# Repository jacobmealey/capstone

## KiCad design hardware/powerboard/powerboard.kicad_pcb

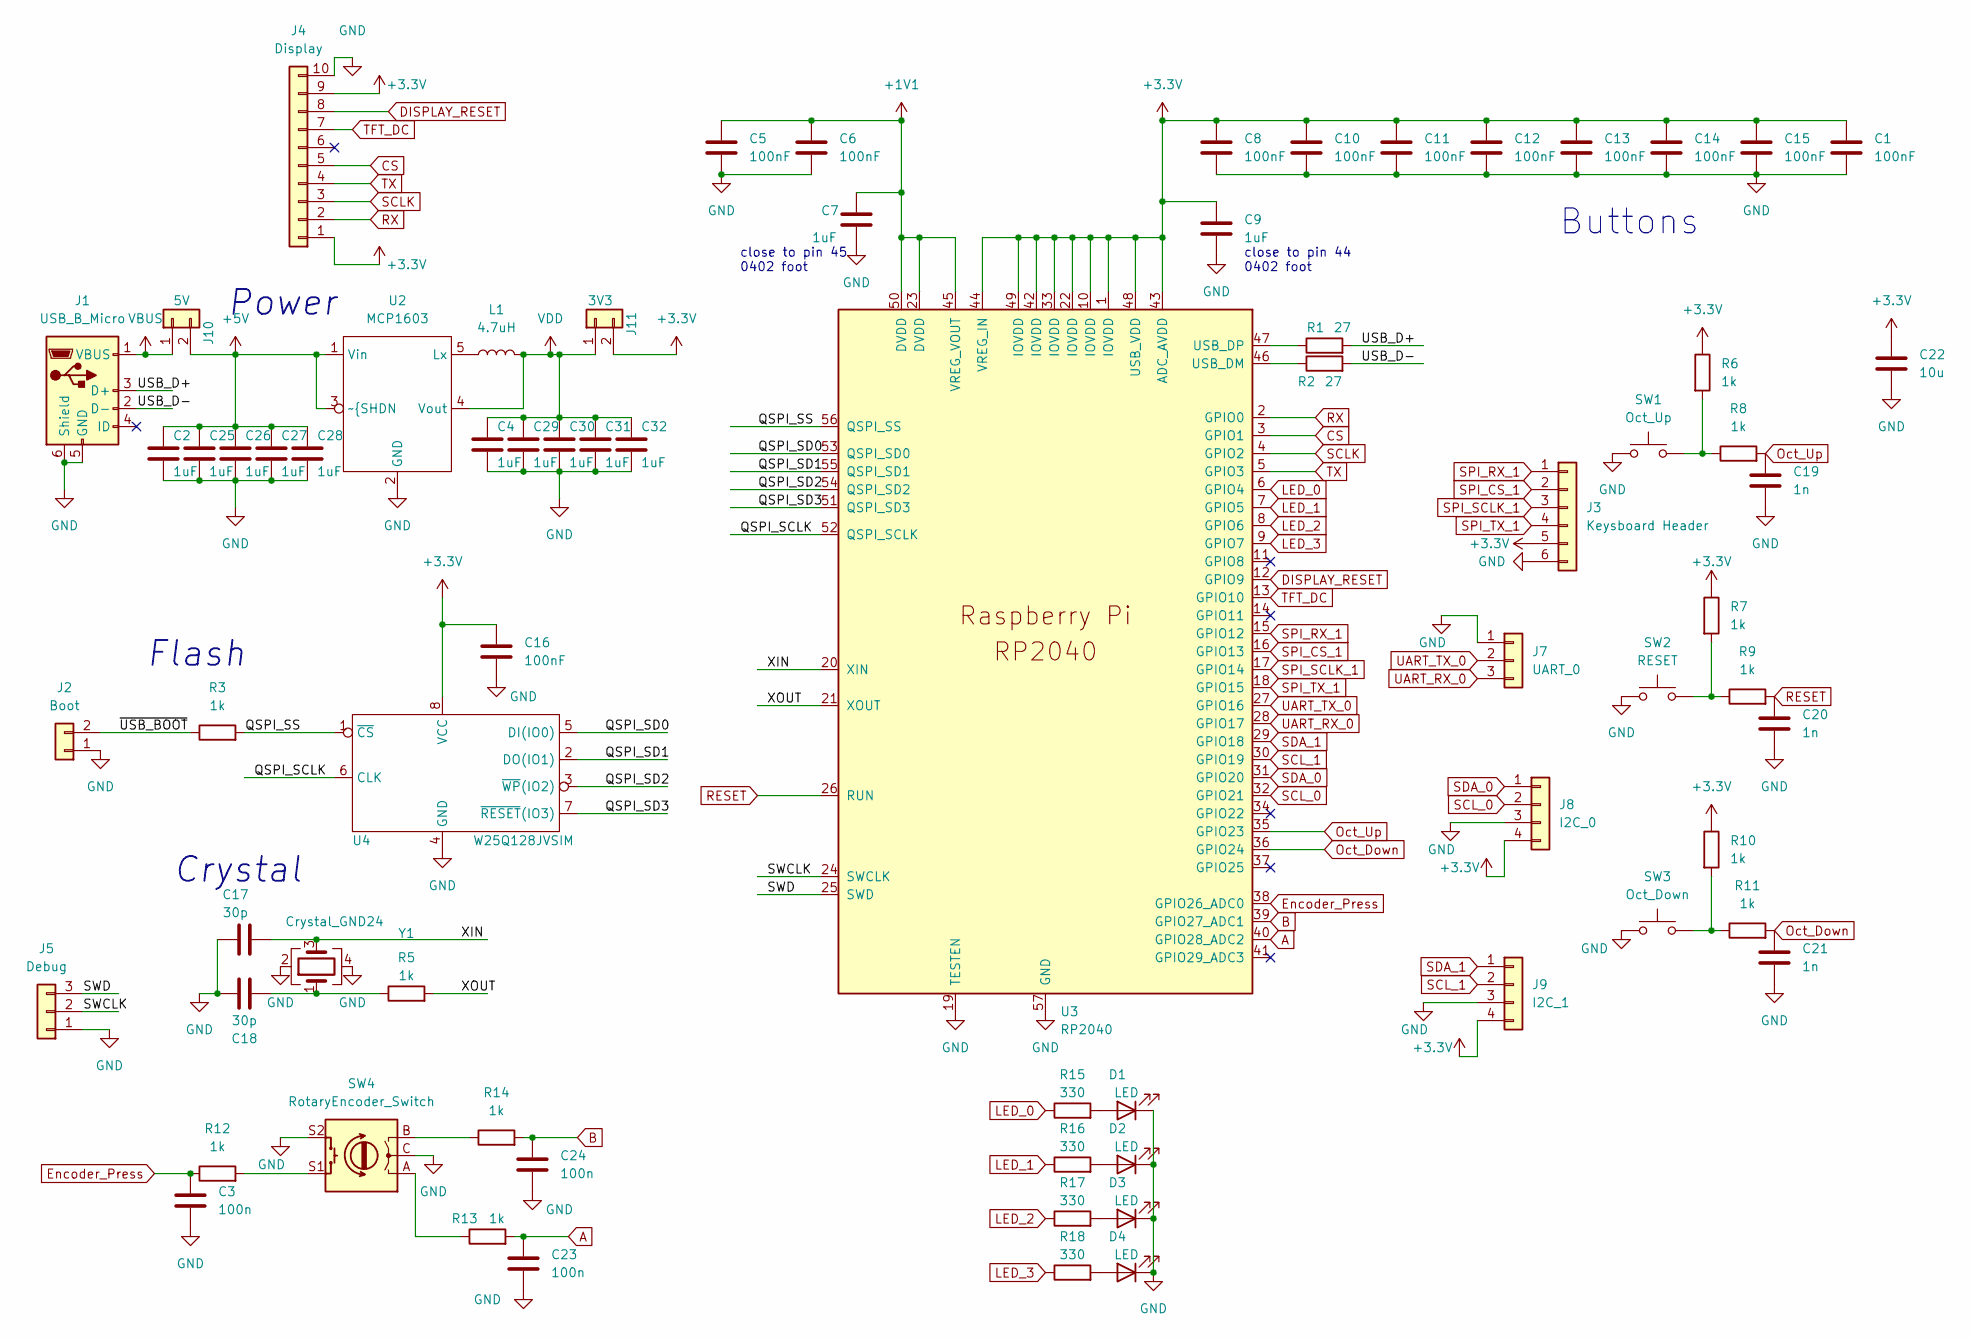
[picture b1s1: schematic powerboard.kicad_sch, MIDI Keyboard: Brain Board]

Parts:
C1, C5, C6, C8, C10, C11, C12, C13, C14, C15: 100nF; C_0402_1005Metric; LCSC C307331
C2, C4, C25, C26, C27, C28, C29, C30, C31, C32: 1uF; C_0805_2012Metric; LCSC C28323
C3, C23, C24: 100n; C_0402_1005Metric; LCSC C307331
C7, C9: 1uF; C_0402_1005Metric; LCSC C307413
C16: 100nF; C_0603_1608Metric; LCSC C307331
C17, C18: 30p; C_0603_1608Metric; LCSC C1658
C19, C20, C21: 1n; C_0603_1608Metric; LCSC C1588
C22: 10u; C_0805_2012Metric; LCSC C440198
D1, D2, D3, D4: LED; LED_0603_1608Metric; LCSC C87326
J1: USB_B_Micro; USB_Micro-B_Amphenol_10118194_Horizontal; LCSC C132563
J2: Boot; PinHeader_1x02_P2.54mm_Vertical; LCSC C2905434
J3: Keysboard Header; PinSocket_1x06_P2.54mm_Horizontal; LCSC C2932681
J4: Display; PinSocket_1x10_P2.54mm_Vertical; LCSC C2905418
J5: Debug; PinHeader_1x03_P2.54mm_Vertical; LCSC C2932698
J7: UART_0; PinHeader_1x03_P2.54mm_Vertical; LCSC C2932698
J8: I2C_0; PinHeader_1x04_P2.54mm_Vertical; LCSC C2905435
J9: I2C_1; PinHeader_1x04_P2.54mm_Vertical; LCSC C2905435
J10: 5V; PinHeader_1x02_P2.54mm_Vertical; LCSC C2905434
J11: 3V3; PinHeader_1x02_P2.54mm_Vertical; LCSC C2905434
L1: 4.7uH; L_1812_4532Metric; LCSC C701275
R1, R2: 27; R_0402_1005Metric; LCSC C25100
R3, R5, R6, R7, R8, R9, R10, R11, R12, R13, R14: 1k; R_0603_1608Metric; LCSC C21190
R15, R16, R17, R18: 330; R_0603_1608Metric; LCSC C23138
SW1: Oct_Up; SW_PUSH_6mm; LCSC C428628
SW2: RESET; SW_PUSH_6mm; LCSC C428628
SW3: Oct_Down; SW_PUSH_6mm; LCSC C428628
SW4: RotaryEncoder_Switch; RotaryEncoder_Alps_EC11E-Switch_Vertical_H20mm; LCSC C278348
U2: MCP1603; TSOT-23-5; LCSC C150803
U3: RP2040; RP2040-QFN-56; LCSC C9900024873
U4: W25Q128JVSIM; SOIC-8W_5.3x5.3mm_P1.27mm; LCSC C2613930
Y1: Crystal_GND24; Crystal_SMD_3225-4Pin_3.2x2.5mm; LCSC C133334

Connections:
+1V1: C5.1, C6.1, C7.1, U3.23 (DVDD), U3.45 (VREG_VOUT), U3.50 (DVDD)
+3.3V: C1.1, C8.1, C9.1, C10.1, C11.1, C12.1, C13.1, C14.1, C15.1, C16.1, C22.1, J3.5, J4.1, J4.9, J8.4, J9.4, J11.2, R6.1, R7.1, R10.1, U3.1 (IOVDD), U3.10 (IOVDD), U3.22 (IOVDD), U3.33 (IOVDD), U3.42 (IOVDD), U3.43 (ADC_AVDD), U3.44 (VREG_IN), U3.48 (USB_VDD), U3.49 (IOVDD), U4.8 (VCC)
+5V: C2.1, C25.1, C26.1, C27.1, C28.1, J10.2, U2.1 (Vin), U2.3 (~{SHDN)
/QSPI_SCLK: U3.52 (QSPI_SCLK), U4.6 (CLK)
/QSPI_SD0: U3.53 (QSPI_SD0), U4.5 (DI(IO0))
/QSPI_SD1: U3.55 (QSPI_SD1), U4.2 (DO(IO1))
/QSPI_SD2: U3.54 (QSPI_SD2), U4.3 (~WP(IO2))
/QSPI_SD3: U3.51 (QSPI_SD3), U4.7 (~RESET(IO3))
/QSPI_SS: R3.2, U3.56 (QSPI_SS), U4.1 (~CS)
/SWCLK: J5.2, U3.24 (SWCLK)
/SWD: J5.3, U3.25 (SWD)
/USB_D+: J1.3 (D+), R1.2
/USB_D-: J1.2 (D-), R2.2
/XIN: C17.2, U3.20 (XIN), Y1.3
/XOUT: R5.2, U3.21 (XOUT)
/~USB_BOOT: J2.2, R3.1
A: C23.1, R13.2, U3.40 (GPIO28_ADC2)
B: C24.1, R14.2, U3.39 (GPIO27_ADC1)
CS: J4.5, U3.3 (GPIO1)
DISPLAY_RESET: J4.8, U3.12 (GPIO9)
Encoder_Press: C3.1, R12.1, U3.38 (GPIO26_ADC0)
GND: C1.2, C2.2, C3.2, C4.2, C5.2, C6.2, C7.2, C8.2, C9.2, C10.2, C11.2, C12.2, C13.2, C14.2, C15.2, C16.2, C17.1, C18.1, C19.2, C20.2, C21.2, C22.2, C23.2, C24.2, C25.2, C26.2, C27.2, C28.2, C29.2, C30.2, C31.2, C32.2, D1.1 (K), D2.1 (K), D3.1 (K), D4.1 (K), J1.5 (GND), J1.6 (Shield), J2.1, J3.6, J4.10, J5.1, J7.1, J8.3, J9.3, SW1.1, SW2.1, SW3.1, SW4.C, SW4.S2, U2.2 (GND), U3.19 (TESTEN), U3.57 (GND), U4.4 (GND), Y1.2, Y1.4
LED_0: R15.1, U3.6 (GPIO4)
LED_1: R16.1, U3.7 (GPIO5)
LED_2: R17.1, U3.8 (GPIO6)
LED_3: R18.1, U3.9 (GPIO7)
unnamed: C18.2, R5.1, Y1.1
unnamed: D1.2 (A), R15.2
unnamed: D2.2 (A), R16.2
unnamed: D3.2 (A), R17.2
unnamed: D4.2 (A), R18.2
unnamed: L1.1, U2.5 (Lx)
unnamed: R1.1, U3.47 (USB_DP)
unnamed: R2.1, U3.46 (USB_DM)
unnamed: R6.2, R8.1, SW1.2
unnamed: R7.2, R9.1, SW2.2
unnamed: R10.2, R11.1, SW3.2
unnamed: R12.2, SW4.S1
unnamed: R13.1, SW4.A
unnamed: R14.1, SW4.B
Oct_Down: C21.1, R11.2, U3.36 (GPIO24)
Oct_Up: C19.1, R8.2, U3.35 (GPIO23)
RESET: C20.1, R9.2, U3.26 (RUN)
RX: J4.2, U3.2 (GPIO0)
SCLK: J4.3, U3.4 (GPIO2)
SCL_0: J8.2, U3.32 (GPIO21)
SCL_1: J9.2, U3.30 (GPIO19)
SDA_0: J8.1, U3.31 (GPIO20)
SDA_1: J9.1, U3.29 (GPIO18)
SPI_CS_1: J3.2, U3.16 (GPIO13)
SPI_RX_1: J3.1, U3.15 (GPIO12)
SPI_SCLK_1: J3.3, U3.17 (GPIO14)
SPI_TX_1: J3.4, U3.18 (GPIO15)
TFT_DC: J4.7, U3.13 (GPIO10)
TX: J4.4, U3.5 (GPIO3)
UART_RX_0: J7.3, U3.28 (GPIO17)
UART_TX_0: J7.2, U3.27 (GPIO16)
VBUS: J1.1 (VBUS), J10.1
VDD: C4.1, C29.1, C30.1, C31.1, C32.1, J11.1, L1.2, U2.4 (Vout)

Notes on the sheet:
Power
Buttons
Flash
Crystal
close to pin 44 0402 foot
close to pin 45 0402 foot

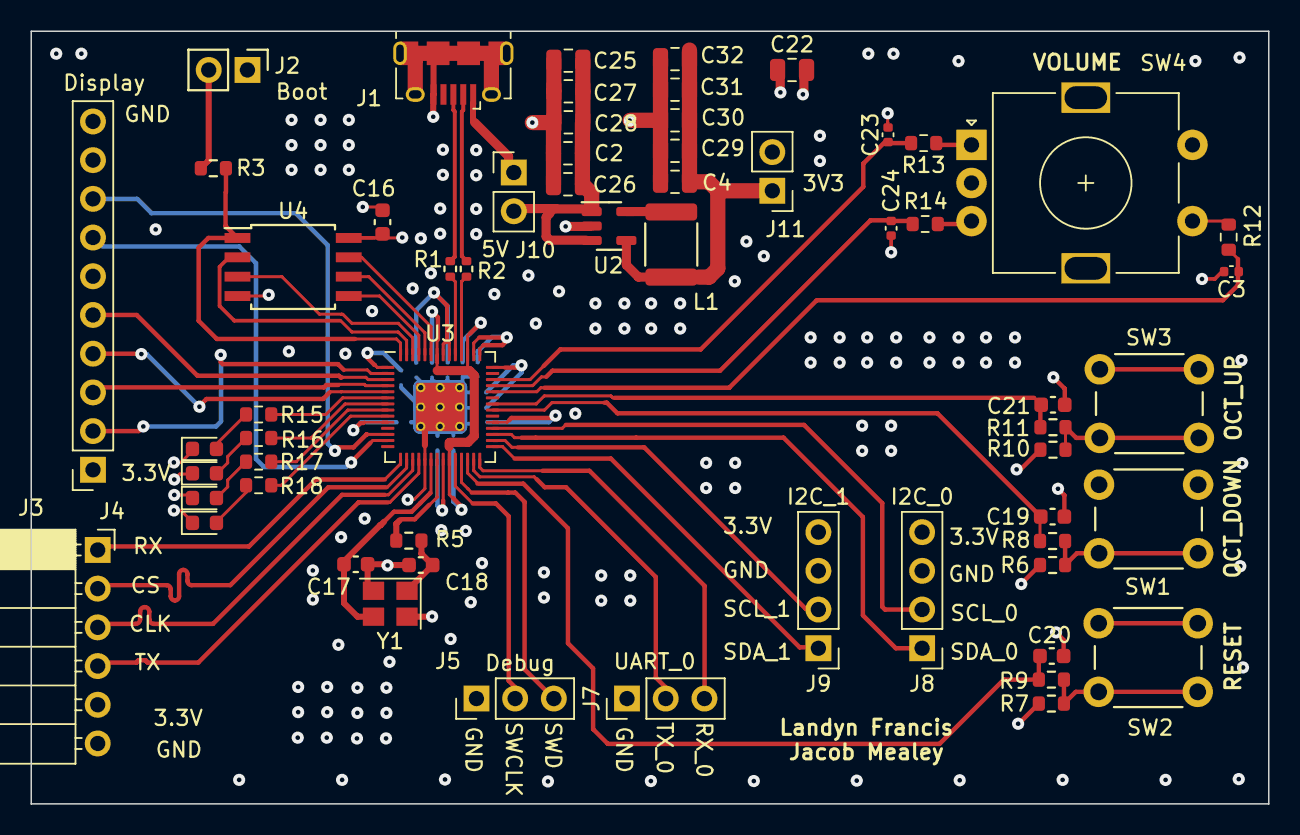
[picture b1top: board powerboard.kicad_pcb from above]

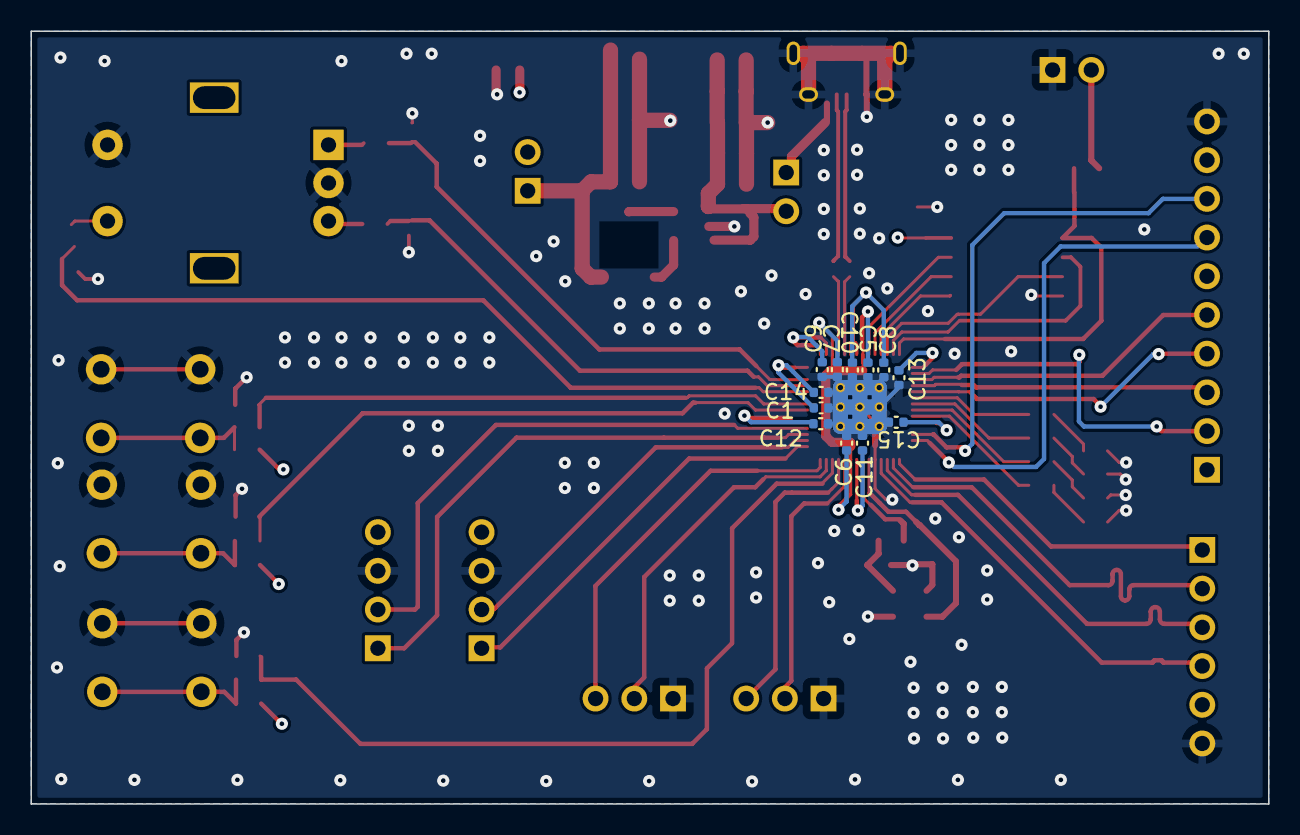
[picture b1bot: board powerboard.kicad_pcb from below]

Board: 4 copper layers, 81.2 x 50.7 mm, 72 parts (12 on the bottom side), 59 nets.

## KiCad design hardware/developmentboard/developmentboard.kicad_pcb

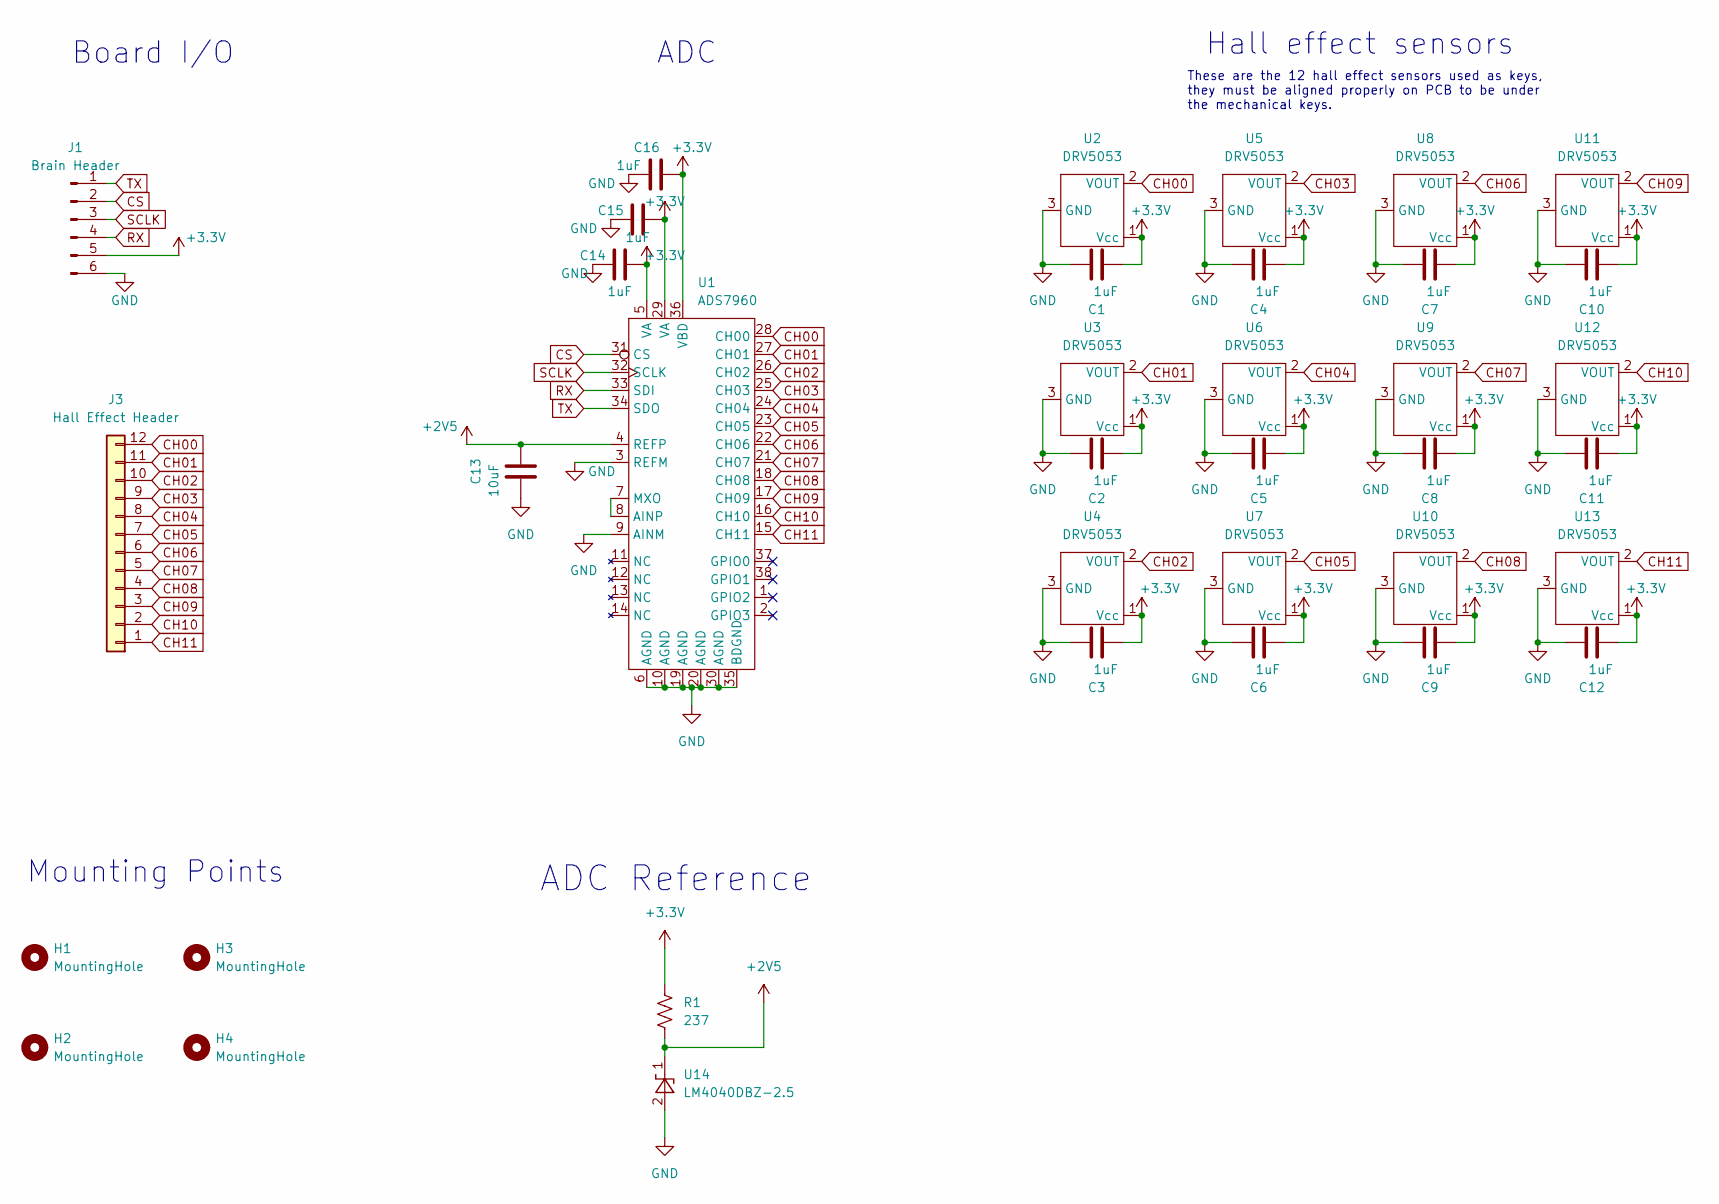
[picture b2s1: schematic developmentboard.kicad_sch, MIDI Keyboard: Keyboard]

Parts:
C1, C2, C3, C4, C5, C6, C7, C8, C9, C10, C11, C12, C14, C15, C16: 1uF; C_0603_1608Metric; LCSC C90540
C13: 10uF; C_0603_1608Metric; LCSC C96446
H1, H2, H3, H4: MountingHole; MountingHole_4.3mm_M4
J1: Brain Header; PinHeader_1x06_P2.54mm_Vertical; LCSC C2932681
J3: Hall Effect Header; PinHeader_1x12_P2.54mm_Vertical; LCSC C2833334
R1: 237; R_1210_3225Metric; part number CR1210F237RP05Z; LCSC C174455
U1: ADS7960; TSSOP-38_4.4x9.7mm_P0.5mm; LCSC C1543353
U2, U3, U4, U5, U6, U7, U8, U9, U10, U11, U12, U13: DRV5053; SOT-23; LCSC C2866569
U14: LM4040DBZ-2.5; SOT-23; LCSC C134019

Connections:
+2V5: C13.1, R1.2, U1.4 (REFP), U14.1 (K)
+3.3V: C1.2, C2.2, C3.2, C4.2, C5.2, C6.2, C7.2, C8.2, C9.2, C10.2, C11.2, C12.2, C14.2, C15.2, C16.2, J1.5, R1.1, U1.5 (VA), U1.29 (VA), U1.36 (VBD), U2.1 (Vcc), U3.1 (Vcc), U4.1 (Vcc), U5.1 (Vcc), U6.1 (Vcc), U7.1 (Vcc), U8.1 (Vcc), U9.1 (Vcc), U10.1 (Vcc), U11.1 (Vcc), U12.1 (Vcc), U13.1 (Vcc)
CH00: J3.12, U1.28 (CH00), U2.2 (VOUT)
CH01: J3.11, U1.27 (CH01), U3.2 (VOUT)
CH02: J3.10, U1.26 (CH02), U4.2 (VOUT)
CH03: J3.9, U1.25 (CH03), U5.2 (VOUT)
CH04: J3.8, U1.24 (CH04), U6.2 (VOUT)
CH05: J3.7, U1.23 (CH05), U7.2 (VOUT)
CH06: J3.6, U1.22 (CH06), U8.2 (VOUT)
CH07: J3.5, U1.21 (CH07), U9.2 (VOUT)
CH08: J3.4, U1.18 (CH08), U10.2 (VOUT)
CH09: J3.3, U1.17 (CH09), U11.2 (VOUT)
CH10: J3.2, U1.16 (CH10), U12.2 (VOUT)
CH11: J3.1, U1.15 (CH11), U13.2 (VOUT)
CS: J1.2, U1.31 (CS)
GND: C1.1, C2.1, C3.1, C4.1, C5.1, C6.1, C7.1, C8.1, C9.1, C10.1, C11.1, C12.1, C13.2, C14.1, C15.1, C16.1, J1.6, U1.3 (REFM), U1.6 (AGND), U1.9 (AINM), U1.10 (AGND), U1.19 (AGND), U1.20 (AGND), U1.30 (AGND), U1.35 (BDGND), U2.3 (GND), U3.3 (GND), U4.3 (GND), U5.3 (GND), U6.3 (GND), U7.3 (GND), U8.3 (GND), U9.3 (GND), U10.3 (GND), U11.3 (GND), U12.3 (GND), U13.3 (GND), U14.2 (A)
unnamed: U1.7 (MXO), U1.8 (AINP)
RX: J1.4, U1.33 (SDI)
SCLK: J1.3, U1.32 (SCLK)
TX: J1.1, U1.34 (SDO)

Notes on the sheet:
Board I/O
Hall effect sensors
ADC
Mounting Points
ADC Reference
These are the 12 hall effect sensors used as keys, they must be aligned properly on PCB to be under the mechanical keys.

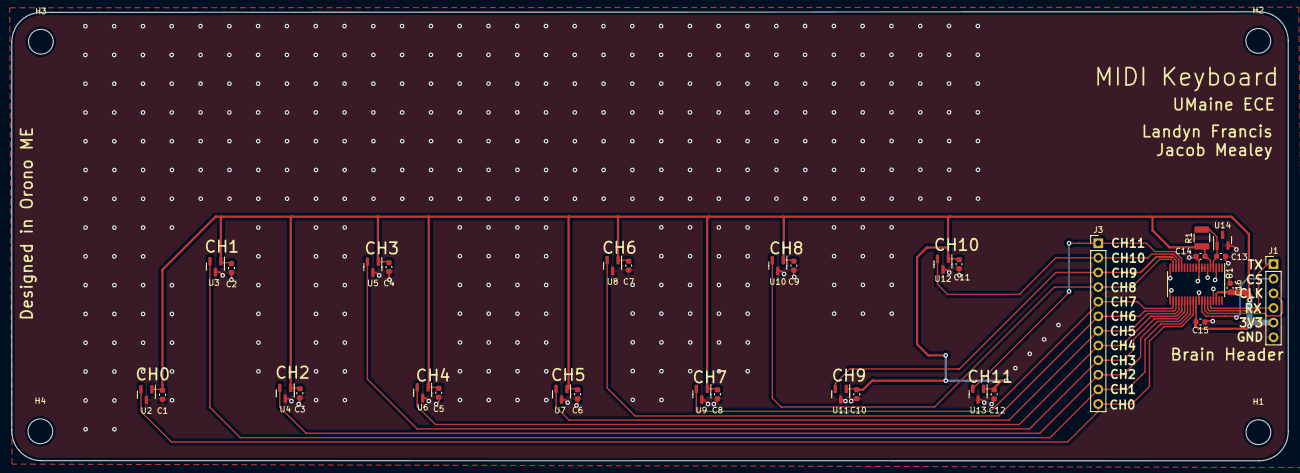
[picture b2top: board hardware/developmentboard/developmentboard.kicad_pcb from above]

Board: 2 copper layers, 221.8 x 78.0 mm, 37 parts (0 on the bottom side), 20 nets.

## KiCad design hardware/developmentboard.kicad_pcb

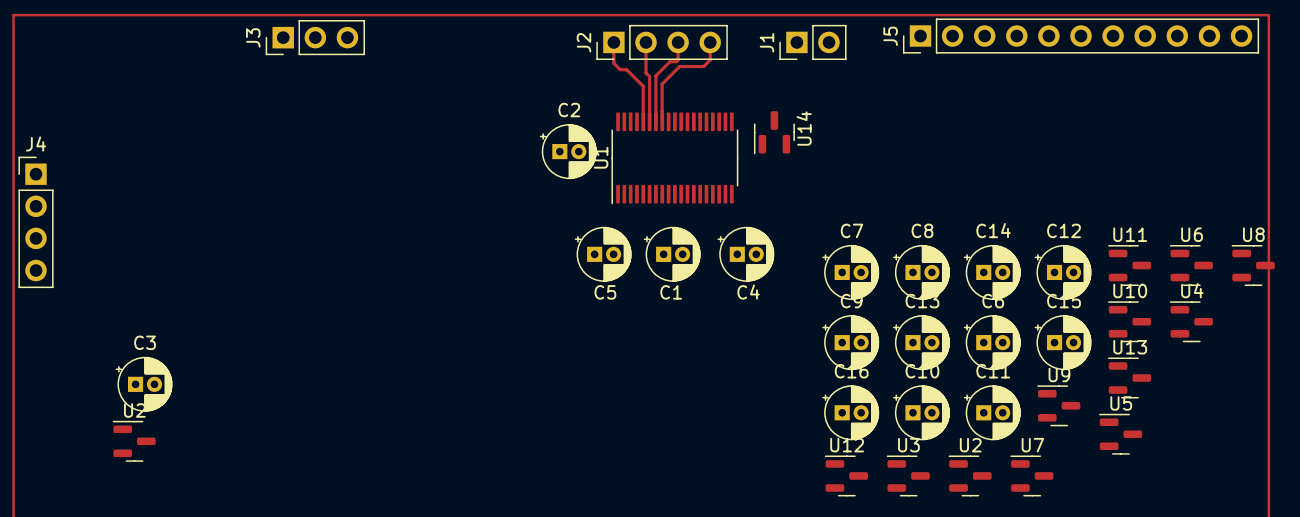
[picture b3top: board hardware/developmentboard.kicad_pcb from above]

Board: 2 copper layers, 36 parts (0 on the bottom side), 26 nets.

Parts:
C1: 10u; CP_Radial_D4.0mm_P1.50mm
C2, C6, C7, C8, C9, C10, C11, C12, C13, C14, C15, C16: C_Small; CP_Radial_D4.0mm_P1.50mm
C3, C4, C5: 1u; CP_Radial_D4.0mm_P1.50mm
J1: MXO AINP; PinHeader_1x02_P2.54mm_Vertical
J2: SPI Header; PinHeader_1x04_P2.54mm_Vertical
J3: Power; PinHeader_1x03_P2.54mm_Vertical
J4: GPIO; PinHeader_1x04_P2.54mm_Vertical
J5: Channel Breakout; PinHeader_1x11_P2.54mm_Vertical
U1: ADS7960; TSSOP-38_4.4x9.7mm_P0.5mm
U2, U3, U4, U5, U6, U7, U8, U9, U10, U11, U12, U13: DRV5055A1xDBZxQ1; SOT-23
U2#2: DRV5053VAQDBZR; SOT-23
U14: AP2138N-2.5TRG1; SOT-23

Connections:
CH0: U1.28 (CH0), U2#2.2 (VOUT), U4.2 (OUT)
CH1: J5.1, U1.27 (CH1), U5.2 (OUT)
CH2: J5.2, U1.26 (CH2), U8.2 (OUT)
CH3: J5.3, U1.25 (CH3), U11.2 (OUT)
CH4: J5.4, U1.24 (CH4), U2.2 (OUT)
CH5: J5.5, U1.23 (CH5), U6.2 (OUT)
CH6: J5.6, U1.22 (CH6), U9.2 (OUT)
CH7: J5.7, U1.21 (CH7), U12.2 (OUT)
CH8: J5.8, U1.18 (CH8), U3.2 (OUT)
CH9: J5.9, U1.17 (CH9), U7.2 (OUT)
CH10: J5.10, U1.16 (CH10), U10.2 (OUT)
CH11: J5.11, U1.15 (CH11), U13.2 (OUT)
GND: C1.2, C2.2, C3.2, C4.2, C5.2, C6.2, C7.2, C8.2, C9.2, C10.2, C11.2, C12.2, C13.2, C14.2, C15.2, C16.2, J3.3, U1.3 (REFM), U1.6 (AGND), U1.9 (AINM), U1.10 (AGND), U1.11 (NC), U1.12 (NC), U1.13 (NC), U1.14 (NC), U1.19 (AGND), U1.20 (AGND), U1.30 (AGND), U1.35 (BDGND), U2.3 (GND), U2#2.3 (GND), U3.3 (GND), U4.3 (GND), U5.3 (GND), U6.3 (GND), U7.3 (GND), U8.3 (GND), U9.3 (GND), U10.3 (GND), U11.3 (GND), U12.3 (GND), U13.3 (GND), U14.1 (GND)
unnamed: J1.1, U1.7 (MX0)
unnamed: J1.2, U1.8 (AINP)
unnamed: J2.1, U1.34 (SDO)
unnamed: J2.2, U1.33 (SDI)
unnamed: J2.3, U1.32 (SCLK)
unnamed: J2.4, U1.31 (CS)
unnamed: C3.1, J3.2, U1.36 (+VBD)
unnamed: J4.1, U1.37 (GPIO0)
unnamed: J4.2, U1.38 (GPIO1)
unnamed: J4.3, U1.1 (GPIO2)
unnamed: J4.4, U1.2 (GPIO3)
VA: C2.1, C4.1, C5.1, C6.1, C7.1, C8.1, C9.1, C10.1, C11.1, C12.1, C13.1, C14.1, C15.1, C16.1, J3.1, U1.5 (+VA), U1.29 (+VA), U2.1 (VCC), U2#2.1 (VCC), U3.1 (VCC), U4.1 (VCC), U5.1 (VCC), U6.1 (VCC), U7.1 (VCC), U8.1 (VCC), U9.1 (VCC), U10.1 (VCC), U11.1 (VCC), U12.1 (VCC), U13.1 (VCC), U14.3 (Vin)
Vref: C1.1, U1.4 (REFP), U14.2 (Vout)

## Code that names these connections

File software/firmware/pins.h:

// File: pins.h
// Date Created: 9/16/22
// Authors: Landyn Francis (landyn.francis@maine.edu) Jacob Mealey (jacob.mealey@maine.edu)
// Purpose: Header file containing GPIO Pin definitions for MIDI Keyboard device

#ifndef PINS_H
#define PINS_H
#include <stdint.h>
#include "hardware/gpio.h"
#include "pico/stdio.h"
#include <stdio.h>

// SPI0 is the Display
#define SPI0_RX 0
#define SPI0_CS 1
#define SPI0_SCLK 2
#define SPI0_TX 3

// Other Display GPIO
#define DISPLAY_RESET 9
#define TFT_DC 10

// Four Status/Debugging LED's
#define LED_0 4
#define LED_1 5
#define LED_2 6
#define LED_3 7

// SPI1 is the ADC
#define SPI1_RX 12
#define SPI1_CS 13
#define SPI1_SCLK 14
#define SPI1_TX 15

// UART for Printing Debug Messages
#define UART0_TX 16
#define UART0_RX 17

// I2C1
#define I2C1_SDA 18
#define I2C1_SCL 19

// I2C0
#define I2C0_SDA 20
#define I2C0_SCL 21

// User Control Buttons
#define OCT_UP 23
#define OCT_DOWN 24

// Volume Dial (Rotary Encoder)
#define ENCODE_PRESS 26
#define ENCODE_B 27
#define ENCODE_A 28

// GPIO Interrupt Callback Function
void gpio_callback(uint gpio, uint32_t events);

// Initialize GPIO Pins
uint8_t pin_init();

// GPIO Event to String
void gpio_event_string(char *buf, uint32_t events);

#endif

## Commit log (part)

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2022-07-16 ??? made a board lol
2022-07-22 added 2.5v regulator and 12 keys
    added 2.5v regulator and 12 keys
    added 2.5v regulator and 12 keys
2022-07-31 migrated to version 6 made new symbols and included in repo
2022-07-31 made ece library parts relative to project
    forgit sym-lib-table
2022-07-31 added hall-effect sensor
2022-07-31 removed extra garbage files
2022-07-31 removed old 'backup' folder
2022-07-31 testing gitignore
2022-07-31 moved gitignore to root
2022-08-04 white keys going crazy
2022-08-04 update gitignore for freecad
2022-08-04 colored keys finished basic assembly
2022-08-08 Development Board Schematic Changes
2022-08-09 3d models lol
2022-08-12 Bypassed Va and Vbd to GND with 1uF AINM to GND Breakout pins for ADC pins
2022-08-15 finalized touches on keyyys + new key mounting
    finalized touches on keyyys + new key mounting
2022-08-22 Powerboard schematic started
2022-08-26 scaffolding for pico project
2022-08-26 Midi demo working in standalone build -- needs testing
    Midi demo working in standalone build -- needs testing
2022-08-29 Adjustment to CMake version requirement
2022-08-31 initial work for SPI ADC
2022-08-31 formatted main.c
2022-09-05 basic SPI working -- need to setup with DMA and timers
2022-09-07 Slight schematic changes
2022-09-08 Schematic Headers Added, Footprints Updated
2022-09-09 Schematics updated, Layout started for powerboard
2022-09-09 Footprint library taken from RP2040 Minimal
2022-09-10 Powerboard PCB Started
    Powerboard PCB Started
    Placed and Routed Power Section, USB Port, Power Header, All Bypass Capacitors, USB Data Lines.
2022-09-11 More PCB Layout
    Board Overhauled
    Crystal Routed
    Bypass Caps on Bottom of Board
    Everything but switches done
    ANNULAR RING PROBLEM
2022-09-12 Power PCB: Everything(?!) Placed
    Added SPI_0 and SPI_1 Headers, for ADC and Display
    Added I2C_0 and I2C_1 Headers, for possible future peripherals, and/or 4 GPIO Pins.
    I assume we don't need UART for anything, so I left it un-routed.
    Everything placed I hope(?), just need to route the buttons and adjust copper zones.
2022-09-12 timer trigger spi write -- need interrupt for recieve
2022-09-12 added irq for receiving spi data
2022-09-12 comment out code for auto-mode 2, fall back to manual
2022-09-12 PCB Adjustments
2022-09-12 USB Header Footprint Changed
    Found a USB Header on JLCAssembly that has a matching footprint in KiCad, W
2022-09-13 manually looping through all channels! + uart for printing. need to get auto modes programmed in!
2022-09-13 auto mode 2 working correctly, cleaned up from last few days in hell
2022-09-13 some more cleaning and comments
2022-09-14 added -Wall -Wextra to compile
2022-09-14 Power Board PCB: UART, LED's Smaller Crystal
    Replaced Old Crystal with 3N12000G33YC
    Added UART_0 with GP16 and GP17
    Added 4 LED's with 330OHM Resistors on GP4-GP7
    SPI Trace Widths 11.55 mil = 50Ohm Impedance
2022-09-15 Scaffolding for keys datastructure
2022-09-15 cleaned up developmentboard
2022-09-15 Initial work on keys pcb
    ADC layout done and inline with the datasheet, and I arranged all the
    hall effect sensors.
2022-09-15 Powerboard almsot done, need to finalize Power Circuit design
2022-09-15 layout for hall effect sensors, imported rules from powerboard
2022-09-15 routing for keys and ground fill under adc
2022-09-16 Pins.h added Pin assignments setup, SPI pins assigned in main.c
2022-09-16 Same as last commit? VS Code buggin
2022-09-18 Powerboard changes
2022-09-18 midi.c and midi.h added MIDI Command set copied into midi.h send_general_midi_message() declared and defined. main.c updated to reflect changes
2022-09-18 board outline for developmentboard
2022-09-18 fized DRC errors
2022-09-18 added more to silkscreen
2022-09-18 added more to silkscreen on developmentboard
2022-09-19 Updated development board reference circuit
    I threw together a circuit based on the REF5025 datasheet to replace the LDO. This is the chip that is recommended on the ADC datasheet for the reference voltage. Available on JLC as REF5025AIDR
2022-09-19 added reference IC to PCB, removed LDO
2022-09-19 main adjustments
2022-09-19 fixed logic for general_midi_send
2022-09-19 update adc to spi1 everywhere, fixed pin definitions
2022-09-19 added volume control function
2022-09-19 more work on midi / adc interface
2022-09-19 MIDI Mute added
2022-09-19 Added keyboard initialization code I don't know if I did this right, so in main.c it's left as a comment.
2022-09-19 comment
2022-09-20 finalized reference IC pcb stuffs - added footprints for bypass caps
2022-09-20 GPIO functions setup? Ready for testing
2022-09-20 gpio base code works
2022-09-21 GPIO Functions done Small footprint changes to powerboard
2022-09-21 Power Measurement Headers
    Added, did not connect power measurement headers.
    Do we need these?
    How do we want to measure power?
    This is a high current, high frequency path, can we even do a header like this?
2022-09-22 mounting holes for keys board
2022-09-22 Powerboard Finalization
    Crystal Footprint and layout changed to match new crystal
2022-09-22 Powerboard review with sheaff
2022-09-22 made development board wider, changed reference voltage to use shunt regulator
2022-09-22 Powerboard PCB Revisions
    Expanded I2C Headers to include 3.3V and GND
    Expanded UART Header to include GND
    Expanded SWD Header to include GND
    Added Silkscreen for All(?) Parts
    Added GND Fill on Back Layer
    Added header for 3.3V and 5V Current Measurements
2022-09-23 more adjustments on powerboard
2022-09-23 JLC Capabilities Double Checked
    Confirmed JLC Capabilities with Design Rules
    CHECK SILKSCREEN RULES
2022-09-23 More powerboard finalization
2022-09-23 Devboard and Powerboard matching headers lined up
2022-09-26 MIDI Messages now only sent on Keypress
2022-09-27 GPIO Added for TFT_DC Display Pin
    Connected GPIO 10 to TFT_DC Pin on Display Header
    DISPLAY_RESET is now Connected to GPIO 9
    pins.h updated accordingly
2022-09-27 powerboard adjustments, bom added
2022-09-27 added display.* and wrote init function / write command. needs testing
2022-09-28 Powerboard Output Files Pt.1
2022-09-29 Tracked gerber files for powerboard
2022-09-29 boards board boards no more 3v3 plane and stuwutching
2022-09-29 GERBERS
2022-09-29 Gerbers and pick and place generated
2022-09-29 Footprint adjusted for W25QJVSIM FLASH
2022-09-29 File Cleanup
    Folder tracking makes me frown
2022-09-29 added pickandplace directory
2022-09-29 Trying to finalize Powerboard PCB
    JLC is being bitchy about the RP2040 and MCP1603, the parts aren't showing up in the part viewer preview window and they are "unselected" for assembly because "coordinate data cannot be found". Very 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
2022-09-30 reworked things on develpoment
2022-10-03 initial code workign with display
2022-10-03 GND Vias and RP2040 Footprint change
    When JLC was acting weird, I changed the footprint of the RP2040 to the generic version without thermal vias. I now want the thermal vias again, as they provide an easy GND connection for the chip.
2022-10-03 RP2040 Footprint Reset - See last commit
2022-10-05 Key current and prev values should be setup?
2022-10-05 changed speed of SPI
2022-10-06 working on ADC and Key integration.
2022-10-06 BIG UPDATE ADC now runs at 200kHz ADC Timer reduced to 60ms No more multi note on's when holding key down MIDI Velocity calculated, currently (49-123) range read_irq() function adjusted Probably need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
2022-10-10 filling screen with easy to use screen array working
2022-10-10 commented screen_to_disp function
2022-10-10 Added comments and font colors
2022-10-12 Starting work on Rotary Encoder
2022-10-12 Rotary Encoder GPIO Code almost works... Interrupts are making it weird...
2022-10-12 Rotary Encoder logic should be correct. I think the A and B lines are bouncy Getting multiple interrupts on a single falling edge. Software debouncing not working...
2022-10-12 accidental deletion
2022-10-13 Volume value safeguarding (no negatives and <128)
2022-10-13 Powerboard Tweaks
    Removed unnecessary header pin vias (lol)
    Adjusted traces
    Cleaned up Bypass Capacitor traces and vias on RP2040
2022-10-13 Still experiencing double interrupts on A and B lines Sometimes on other lines too, but not as bad... Debouncing hardware didn't fix the problem, definitely seems to be a software issue.
2022-10-13 Powerboard Fixes
    Rotary Encoder debouncing hardware fixed (it used to just be a pull up resistor and bypass cap, lol)
    Spaced out GPIO lines as best as I could.
2022-10-13 THICK TRACES
    I went through and replaced 0.2mm traces with 0.293mm traces, for a few reasons.
    1) Thicker = More current, just in case.
    2) This 0.293mm value is impedance matched for 50Ohms (Phil's Lab Video said it's generally a good idea)
    I also gave the power section very very thick traces. I figured why not, it's high frequency stuff, might as well have good thick traces.
    Still passes DRC
2022-10-13 THICKY TRACES
    THICK BOY TRACES GO BRRRRR
2022-10-14 Last Thicky Update
    More thickening
2022-10-14 3.3V Header Fix
    Both sides of the 3.3V header were on the same +3.3V net, this means that the copper fill on Layer 3 would have connected the header, not the jumper we plan to use. This would have likely broken one 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
2022-10-14 More trace spacing
2022-10-17 output file changes AND notes! Octave is now limited between 9 2 which corresponds to a piano range of C8 to C1, there are 3 notes below C1, that we will not be able to produce.
2022-10-22 moved display *magic* to other core
2022-10-26 ADC interrupt cleaned up MIDI signal code moved to main loop keyboard_task() function written
2022-11-01 Removed RESET GPIO predefine, Our RESET line is implemented through toggling the run pin. This happens through a hardware button. Independent of software.
2022-11-01 reset code removal
2022-11-01 tusb uncommented
2022-11-01 REV1 PCB
2022-11-02 Everything but Keysboard and Display tested.
2022-11-02 Powerboard REV2 - R4 Removed
2022-11-03 Little startup sequence added
2022-11-03 SPI_1 Pin error fixed
    I'm a goof. The pins were off by 1. Rev. 1 will work with some additional wires. Rev. 2 will be ordered on my dime
2022-11-03 ADC can be set to Auto2
2022-11-03 Brain Board can now read the keys and send a single MIDI signal for a keypress below the current threshold of 63. Currently tested with only a single key, multi-key tests tomorrow
2022-11-03 changes to 3d models based physical rev1 board
2022-11-07 Display now works with Brain Board
2022-11-07 preliminary work on velocity code -- needs to be measured
2022-11-08 cleaned up adc irq - added scaffolding for new velocity technique i want to explore
2022-11-09 made key velocity logic more stable -- real world velocity looks better
2022-11-10 keys velocity seems to better! needs more testing but much closer to spec
2022-11-10 Rev.2 Boards Headers updated Male on Keysboard, Female on Brainboard
2022-11-15 POWERBOARD REV2
    Haha silkscreen fix for REV2
    OCT UP and OCT DOWN are fixed
2022-11-22 changed milliseconds to microseconds, still displays milliseconds
2022-12-01 finalized more 3d models -- widekey holder
2022-12-01 speed changes for ADC
2022-12-02 WIP: multiple key velocity working, midi velocity broken
2022-12-05 fixed build system?
2022-12-05 comments for adc.* display.*
2022-12-05 Commentz
2022-12-05 Commented Powerboard Schematic/Powerboard V2
    Added comments and organization to Powerboard Schematic.
    Output files are now generated for Powerboard V2
2022-12-05 More comments and usb descriptor
2022-12-05 cleanup and comments on keysboard schematic
2022-12-05 Schemmy Comment Fix
2022-12-07 Keys in spec B-) very cool
2022-12-07 midi velocity fix started
2022-12-07 DESIGN REVIEW READY
2022-12-07 tweak
2022-12-09 enscripted code, autofomatted much of it
2022-12-11 cleaned up usb_descriptors.c
    added comments
